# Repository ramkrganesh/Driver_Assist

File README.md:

# Driver_Assist
This project uses the following modules to assist a driver of a vehicle about waiting for oncoming, following lane, look for pedestrians, look for right before left.  
Modules used are :  
- Arduino Nano
- APDS-9960 Proximity detection module
- DFPlayer Mini, which will be connected to a speaker for voice assist
- NEO 6M GPS, to detect the speed of vehicle

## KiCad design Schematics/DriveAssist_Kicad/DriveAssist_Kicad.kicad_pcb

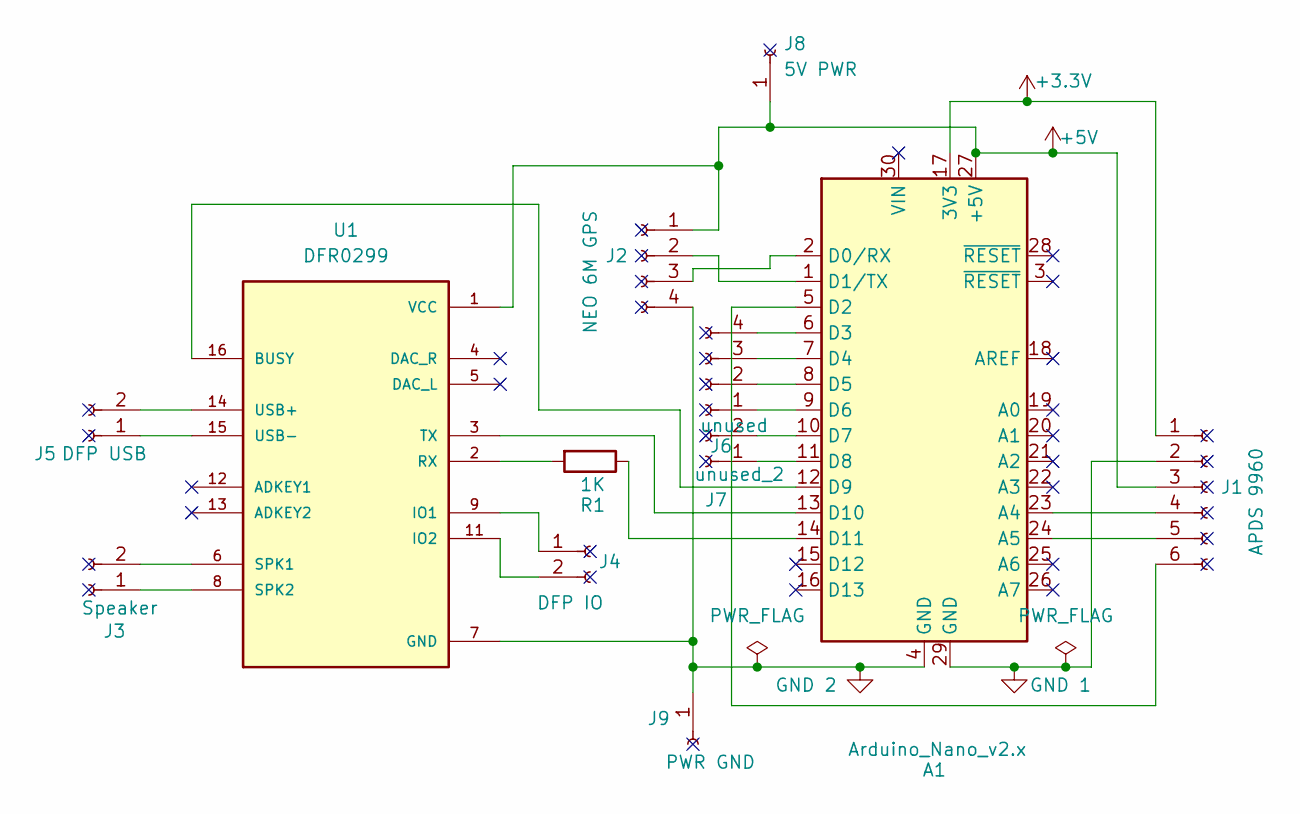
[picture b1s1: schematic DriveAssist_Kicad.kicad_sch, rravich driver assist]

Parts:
A1: Arduino_Nano_v2.x; Arduino_Nano
J1: APDS 9960; PinSocket_1x06_P2.54mm_Vertical
J2: NEO 6M GPS; PinSocket_1x04_P2.54mm_Vertical
J3: Speaker; PinSocket_1x02_P2.54mm_Vertical
J4: DFP IO; PinSocket_1x02_P2.54mm_Vertical
J5: DFP USB; PinSocket_1x02_P2.54mm_Vertical
J6: unused; PinSocket_1x04_P2.54mm_Vertical
J7: unused_2; PinSocket_1x02_P2.54mm_Vertical
J8: 5V PWR; PinSocket_1x01_P2.54mm_Vertical
J9: PWR GND; PinSocket_1x01_P2.54mm_Vertical
R1: 1K; R_Axial_DIN0207_L6.3mm_D2.5mm_P7.62mm_Horizontal
U1: DFR0299; MODULE_DFR0299

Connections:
+3.3V: A1.17 (3V3), J1.1
+5V: A1.27 (+5V), J1.3, J2.1, J8.1, U1.1 (VCC)
GND 1: A1.29 (GND), J1.2
GND 2: A1.4 (GND), J2.4, J9.1, U1.7 (GND), U1.10 (GND)
unnamed: A1.23 (A4), J1.4
unnamed: A1.24 (A5), J1.5
unnamed: A1.2 (D0/RX), J2.3
unnamed: A1.1 (D1/TX), J2.2
unnamed: A1.5 (D2), J1.6
unnamed: A1.6 (D3), J6.4
unnamed: A1.7 (D4), J6.3
unnamed: A1.8 (D5), J6.2
unnamed: A1.9 (D6), J6.1
unnamed: A1.10 (D7), J7.2
unnamed: A1.11 (D8), J7.1
unnamed: A1.12 (D9), U1.16 (BUSY)
unnamed: A1.13 (D10), U1.3 (TX)
unnamed: A1.14 (D11), R1.1
unnamed: J3.1, U1.8 (SPK2)
unnamed: J3.2, U1.6 (SPK1)
unnamed: J4.1, U1.9 (IO1)
unnamed: J4.2, U1.11 (IO2)
unnamed: J5.1, U1.15 (USB-)
unnamed: J5.2, U1.14 (USB+)
unnamed: R1.2, U1.2 (RX)

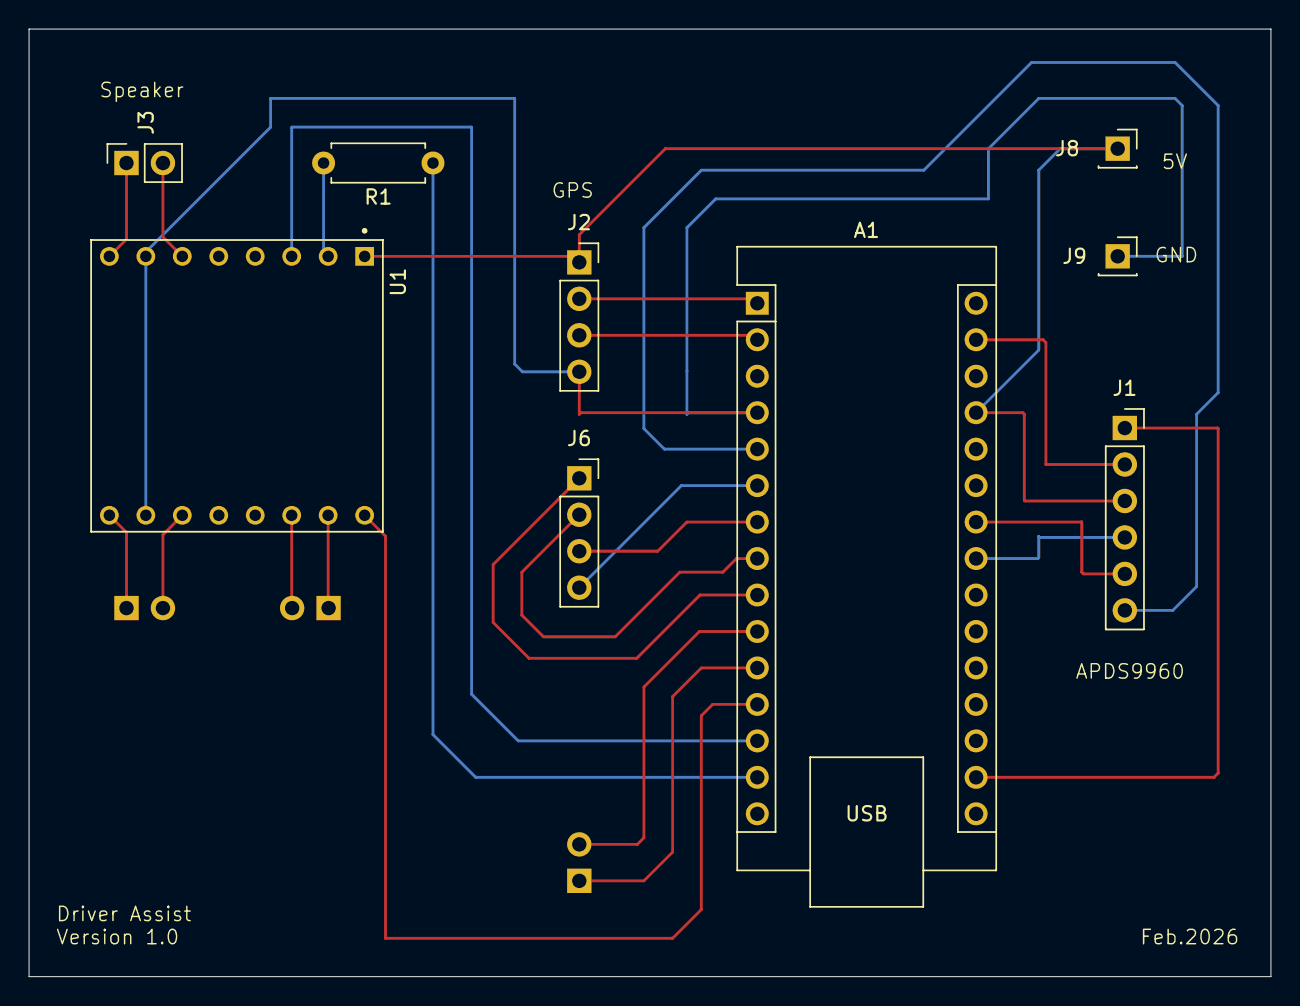
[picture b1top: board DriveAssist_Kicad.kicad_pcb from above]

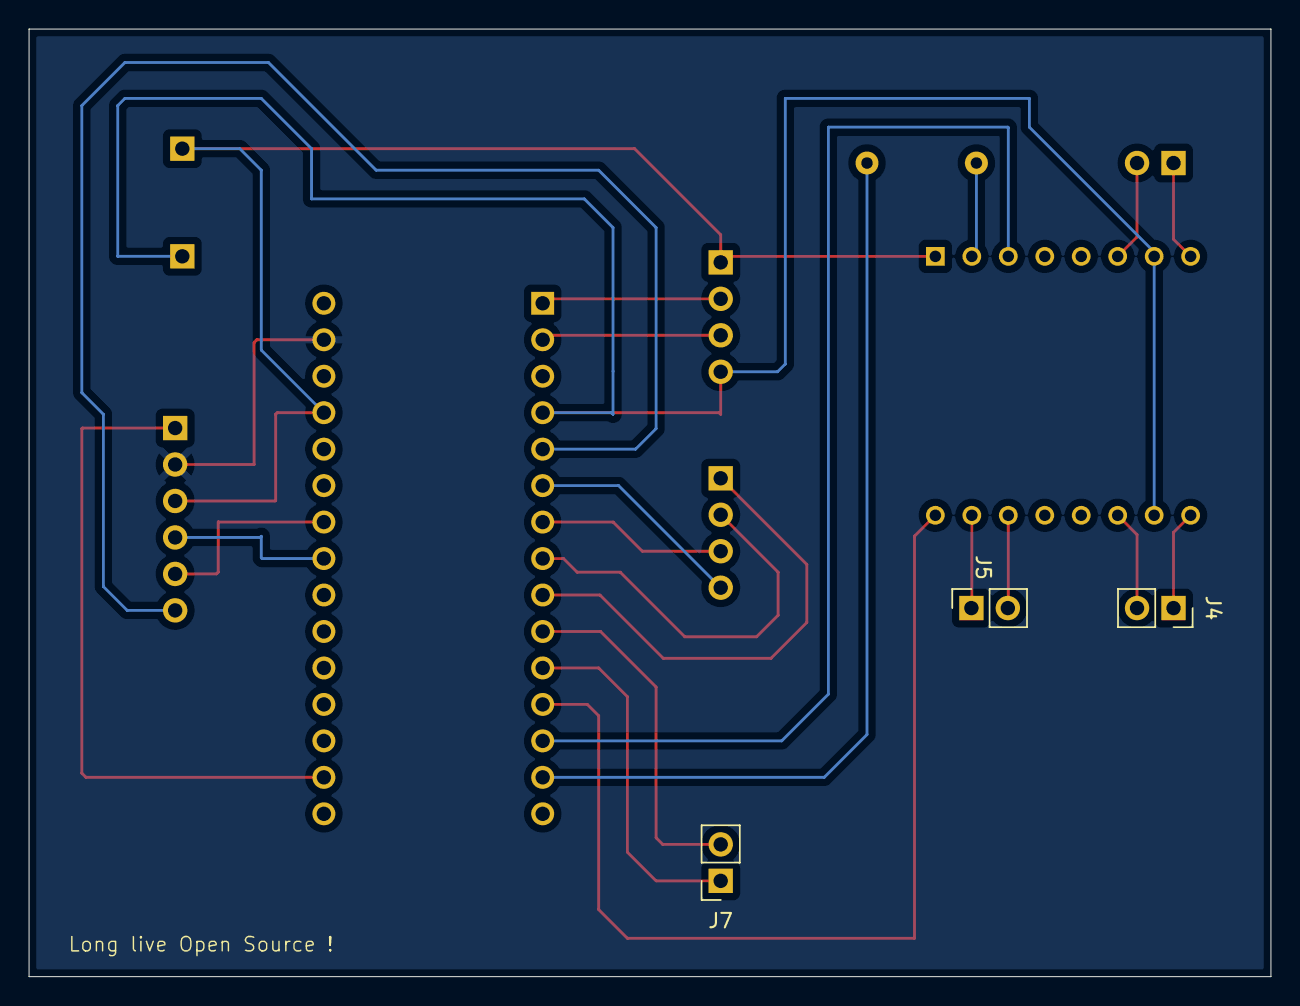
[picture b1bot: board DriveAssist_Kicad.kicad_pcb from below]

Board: 2 copper layers, 86.5 x 66.0 mm, 12 parts (3 on the bottom side), 25 nets.

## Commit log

2025-11-13 working cmake configuration
2025-11-13 updating the skeleton for 9960 driver
2025-11-14 will use proximity detection instead of gesture. Renamed files accordingly.
2025-11-17 minimum code for proximity detection
2025-11-17 cmake update to enable flashing to nano
2025-11-19 temporary commit : it contains lots of test code. heavy refactor and redesign needed
2025-11-19 draw io header structure
2025-11-19 header structure included as a png file
2025-11-20 reordered header file inclusions. Init function for APDS9960 in progress
2025-11-22 implemented initialization sequence for 9960
2025-11-22 starting to use proximity sensor functionality in Driver_Assist.ino
2025-11-22 Implemented code in main loop to get indicator stalk position.
2025-11-22 Proximity sensor working version
2025-11-23 removed init function for apds9960. The Activate function initializes and activates proximity detection
2025-11-23 Introduced a global function to handle communication with 9960 via i2c
2025-11-29 introducing dfplayer class
2025-11-30 implemented dfplayer class and member functions
2025-12-01 integrated both 9960 and DFPlayer features.
2025-12-04 update of readme and general notes
2025-12-11 add neo 6m library
2025-12-11 update delay for DFPlayer tracks, integrate GPS neo 6m code to main application
2025-12-11 support for right before left
2026-01-07 pin mappings added to notes
2026-01-07 adding DFPlayer mini datasheet
2026-02-14 initial version of hardware schematics
2026-02-14 generated gerber files
2026-06-02 code clean up. No functional updates
